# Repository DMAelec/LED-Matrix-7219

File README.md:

# LED Matrix 7219

## Introduction
The LED Matrix 7219 is a serial controlled 8x8 display using individual LED's. Displays can be cascadable up to 8 modules and you can use any
through hole LED's. Pitch between LED's is 7.62mm(0.3"). The Matrix is wired up to match the FC-16 type modules and is standard Arduino code is compatible.

## Bill of Materials
Reference | Description                         | Part No.  
----------|-------------------------------------|----------------
D1-D64    | 5mm LED, Diffused                   | (Red)LTL2R3KRD-EM (Yellow)LTL2R3KYD-EM (Green)LTL2R3KGD-EM
U1        | LED Display Driver IC, PDIP-24      | MAX7219CNG+
R1        | 30KOhm, 1/4W, Resistor              | CFR-25JB-52-30K
C1        | 0.1uF, 50v, MLCC                    | K104K15X7RF5TL2
C2        | 10uF, 25V, Elec Capacitor           | ECE-A1EKS100I
J1        | Terminal block, 2 pos, 5.08mm       | TB007-508-02BE
J2        | Pin Header, 6 pos, 2 row, Straight  | 67996-106HLF
Misc      | Wire Housing, 6 pos, 2 row          | M20-1070300
Misc      | Crimp, 30 AWG to 22 AWG             | M20-1160042

NOTE: R1= Iset Value, Example given 1.5Vf at 20mA. See MAX7219 datasheet for full table.

## Changes
* Revision 2.0
  * Complete board redesign
  * Fixed LED origin point 
  * Added extra bypass capacitors for U1

* Revision 1.0
  * Initial version

## Links

[FC-16 wiring info](https://majicdesigns.github.io/MD_MAX72XX/page_f_c16.html)

[Arduino Library](https://reference.arduino.cc/reference/en/libraries/md_max72xx/)

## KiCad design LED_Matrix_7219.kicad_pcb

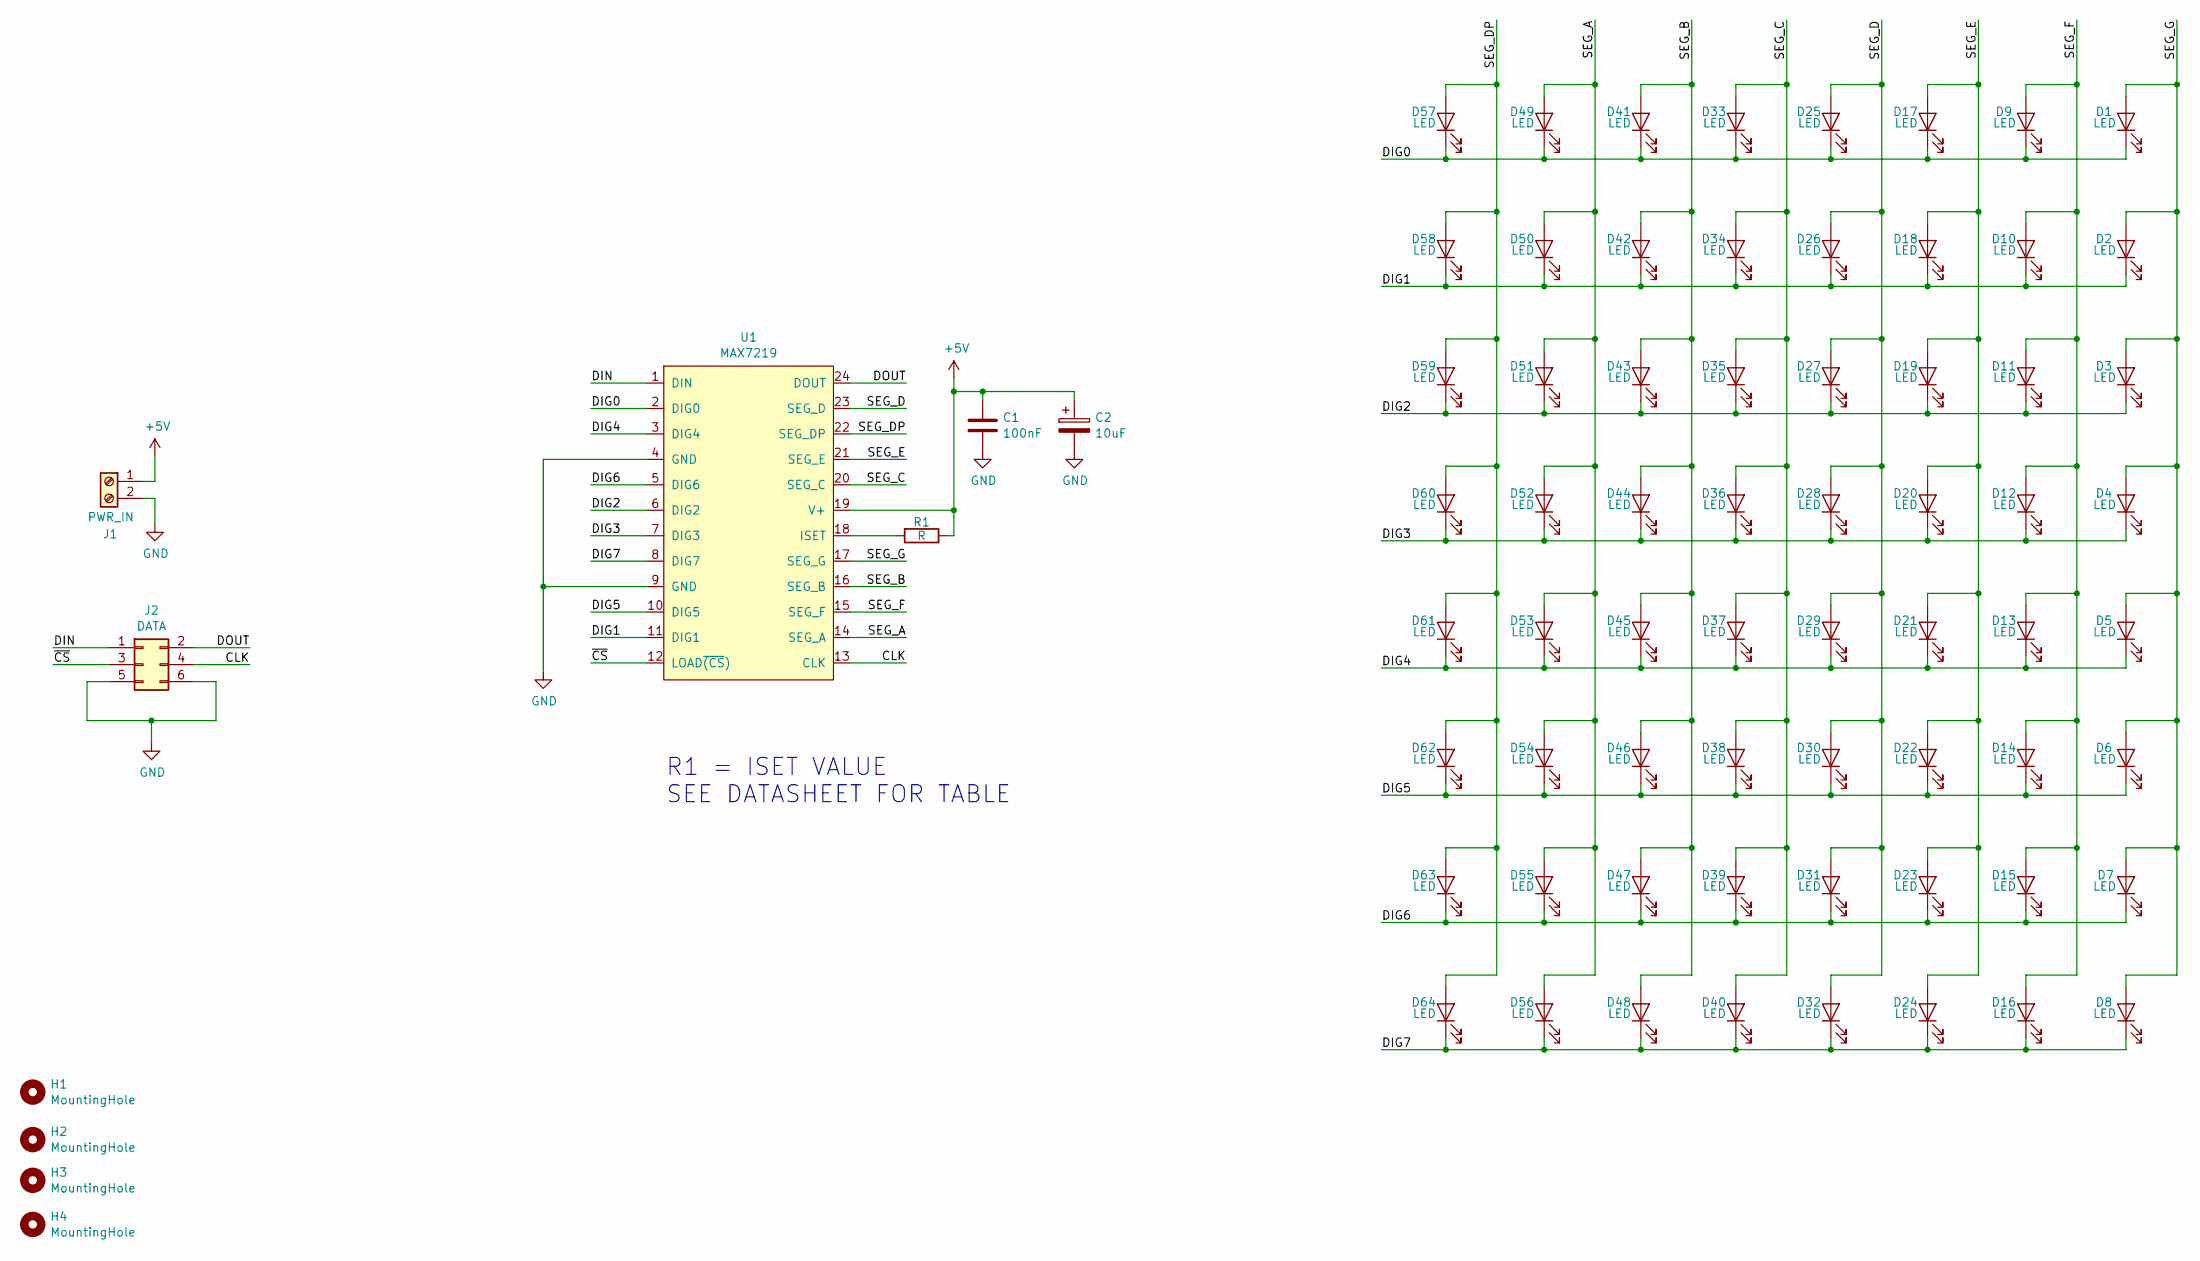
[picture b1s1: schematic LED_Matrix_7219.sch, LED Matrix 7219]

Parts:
C1: 100nF; C_Disc_D3.8mm_W2.6mm_P2.50mm
C2: 10uF; CP_Radial_D5.0mm_P2.50mm
D1, D2, D3, D4, D5, D6, D7, D8, D9, D10, D11, D12, D13, D14, D15, D16, D17, D18, D19, D20, D21, D22, D23, D24, D25, D26, D27, D28, D29, D30, D31, D32, D33, D34, D35, D36, D37, D38, D39, D40, D41, D42, D43, D44, D45, D46, D47, D48, D49, D50, D51, D52, D53, D54, D55, D56, D57, D58, D59, D60, D61, D62, D63, D64: LED; LED_D5.0mm
H1, H2, H3, H4: MountingHole; MountingHole_2.7mm_M2.5
J1: PWR_IN; TerminalBlock_bornier-2_P5.08mm
J2: DATA; PinHeader_2x03_P2.54mm_Vertical
R1: R; R_Axial_DIN0207_L6.3mm_D2.5mm_P7.62mm_Horizontal
U1: MAX7219; DIP-24_W7.62mm

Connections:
+5V: C1.1, C2.1, J1.1, R1.1, U1.19 (V+)
/CLK: J2.4, U1.13 (CLK)
/DIG0: D1.1 (K), D9.1 (K), D17.1 (K), D25.1 (K), D33.1 (K), D41.1 (K), D49.1 (K), D57.1 (K), U1.2 (DIG0)
/DIG1: D2.1 (K), D10.1 (K), D18.1 (K), D26.1 (K), D34.1 (K), D42.1 (K), D50.1 (K), D58.1 (K), U1.11 (DIG1)
/DIG2: D3.1 (K), D11.1 (K), D19.1 (K), D27.1 (K), D35.1 (K), D43.1 (K), D51.1 (K), D59.1 (K), U1.6 (DIG2)
/DIG3: D4.1 (K), D12.1 (K), D20.1 (K), D28.1 (K), D36.1 (K), D44.1 (K), D52.1 (K), D60.1 (K), U1.7 (DIG3)
/DIG4: D5.1 (K), D13.1 (K), D21.1 (K), D29.1 (K), D37.1 (K), D45.1 (K), D53.1 (K), D61.1 (K), U1.3 (DIG4)
/DIG5: D6.1 (K), D14.1 (K), D22.1 (K), D30.1 (K), D38.1 (K), D46.1 (K), D54.1 (K), D62.1 (K), U1.10 (DIG5)
/DIG6: D7.1 (K), D15.1 (K), D23.1 (K), D31.1 (K), D39.1 (K), D47.1 (K), D55.1 (K), D63.1 (K), U1.5 (DIG6)
/DIG7: D8.1 (K), D16.1 (K), D24.1 (K), D32.1 (K), D40.1 (K), D48.1 (K), D56.1 (K), D64.1 (K), U1.8 (DIG7)
/DIN: J2.1, U1.1 (DIN)
/DOUT: J2.2, U1.24 (DOUT)
/SEG_A: D49.2 (A), D50.2 (A), D51.2 (A), D52.2 (A), D53.2 (A), D54.2 (A), D55.2 (A), D56.2 (A), U1.14 (SEG_A)
/SEG_B: D41.2 (A), D42.2 (A), D43.2 (A), D44.2 (A), D45.2 (A), D46.2 (A), D47.2 (A), D48.2 (A), U1.16 (SEG_B)
/SEG_C: D33.2 (A), D34.2 (A), D35.2 (A), D36.2 (A), D37.2 (A), D38.2 (A), D39.2 (A), D40.2 (A), U1.20 (SEG_C)
/SEG_D: D25.2 (A), D26.2 (A), D27.2 (A), D28.2 (A), D29.2 (A), D30.2 (A), D31.2 (A), D32.2 (A), U1.23 (SEG_D)
/SEG_DP: D57.2 (A), D58.2 (A), D59.2 (A), D60.2 (A), D61.2 (A), D62.2 (A), D63.2 (A), D64.2 (A), U1.22 (SEG_DP)
/SEG_E: D17.2 (A), D18.2 (A), D19.2 (A), D20.2 (A), D21.2 (A), D22.2 (A), D23.2 (A), D24.2 (A), U1.21 (SEG_E)
/SEG_F: D9.2 (A), D10.2 (A), D11.2 (A), D12.2 (A), D13.2 (A), D14.2 (A), D15.2 (A), D16.2 (A), U1.15 (SEG_F)
/SEG_G: D1.2 (A), D2.2 (A), D3.2 (A), D4.2 (A), D5.2 (A), D6.2 (A), D7.2 (A), D8.2 (A), U1.17 (SEG_G)
/~CS: J2.3, U1.12 (LOAD~(CS))
GND: C1.2, C2.2, J1.2, J2.5, J2.6, U1.4 (GND), U1.9 (GND)
unnamed: R1.2, U1.18 (ISET)

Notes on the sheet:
R1 = ISET VALUE SEE DATASHEET FOR TABLE

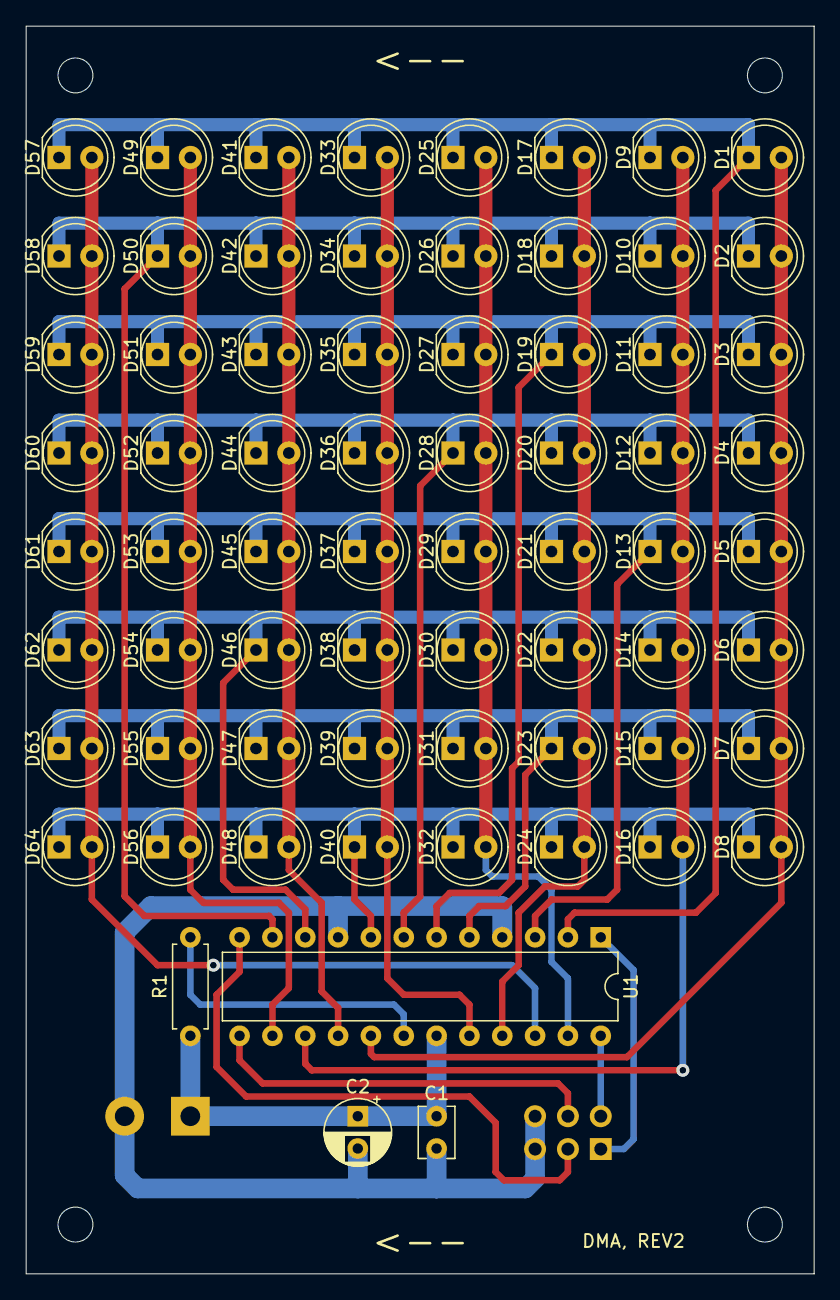
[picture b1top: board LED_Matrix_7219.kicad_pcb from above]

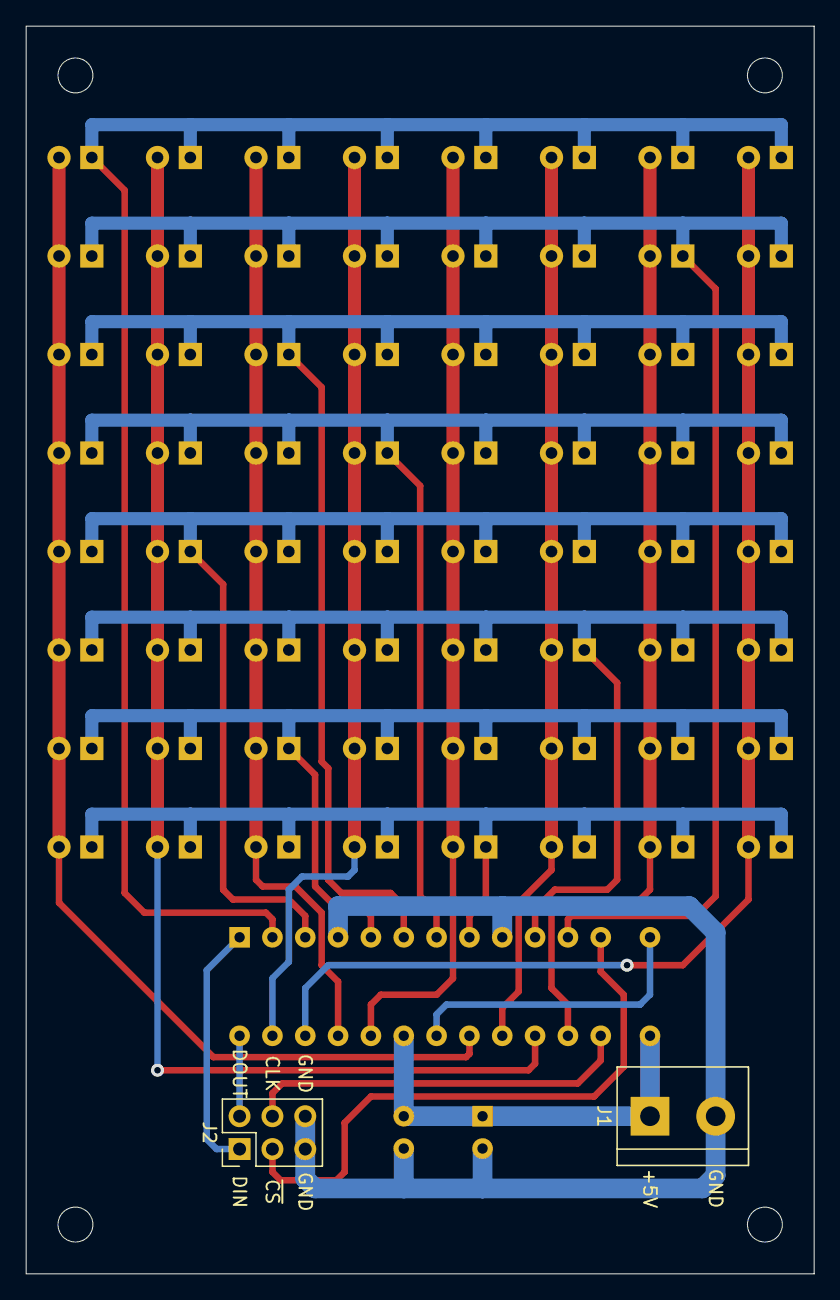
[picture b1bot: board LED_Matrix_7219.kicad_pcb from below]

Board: 2 copper layers, 61.0 x 96.5 mm, 74 parts (2 on the bottom side), 23 nets.
